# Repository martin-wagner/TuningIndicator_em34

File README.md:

TuningIndicator EM34

# TuningIndicator_EM34

Tube in operation

Tube in comparision to a Philips EM34

Youtube:

## Credits

This project is based on retronics.no 6U5 replacement: https://github.com/donpivo/TuningIndicator_6U5

All PCB design files (KiCAD), fabrication files (gerber), 3D models (.stl) and code (C++, PlatformIO) are shared for personal use only; not for commercial use / sale of neither the complete solution nor parts of it.

## Replacement

The EM34 tube is expensive to buy in good condition and doesn't last that long. "Alternative" tubes only have one shadow angles instead of two.
This project creates a long-lasting tube that mimics the two shadow angles of the EM34, including different sensitivity.

## Building

Follow the guide for the 6U5 tube, it's close enough to the EM34: https://retronics.no/2024/08/29/diy-digital-6u5-magic-eye-replacement/
Be aware to use the EM34 BOM, not the 6U5 one!

### LCD

Can be found on Ebay / Aliexpress for approx. 3 Euro. Search terms: _lcd 0.99 12pin_ . Writing _NFP099-01A_ .

### PCB / Housing

Use the gerbers/drill files in cad/pcb/mcu_board/pcb and cad/pcb/octal_base to order at the pcb house of your choise. Use Models/DisplayBracket.stl / Models/EM34-Tube and print/order at the print house of your choise. I've used JLCPCB / JLC3D.

- You need to check your radios schematic for connection of the cathode (see comment in octal_base.pdf).
- I did not use the EMI shield.

### Programming

Use platformio + ST SWD programmer. Either use the programmer on a STM32 devboard or get a ST-LINK/V2 (approx. 15 Euro). Jtag is also exposed on my board, but doesn't have a connector. Use jumper wires to connect SWD to the programmer. The board prints debug info on the serial port.
Be aware that the LCD will not be enabled without pulling the enable pin high (=anode voltage applied)!

### Problems

- The tube is larger compared to a original EM34 (diameter of the top part 30mm instead of 27mm, length 95mm instead of 85mm). Check if your radio will fit a tube of this size!
- The LCD doesn't have good color quality / resolution
- No tube visible when radio is powered off

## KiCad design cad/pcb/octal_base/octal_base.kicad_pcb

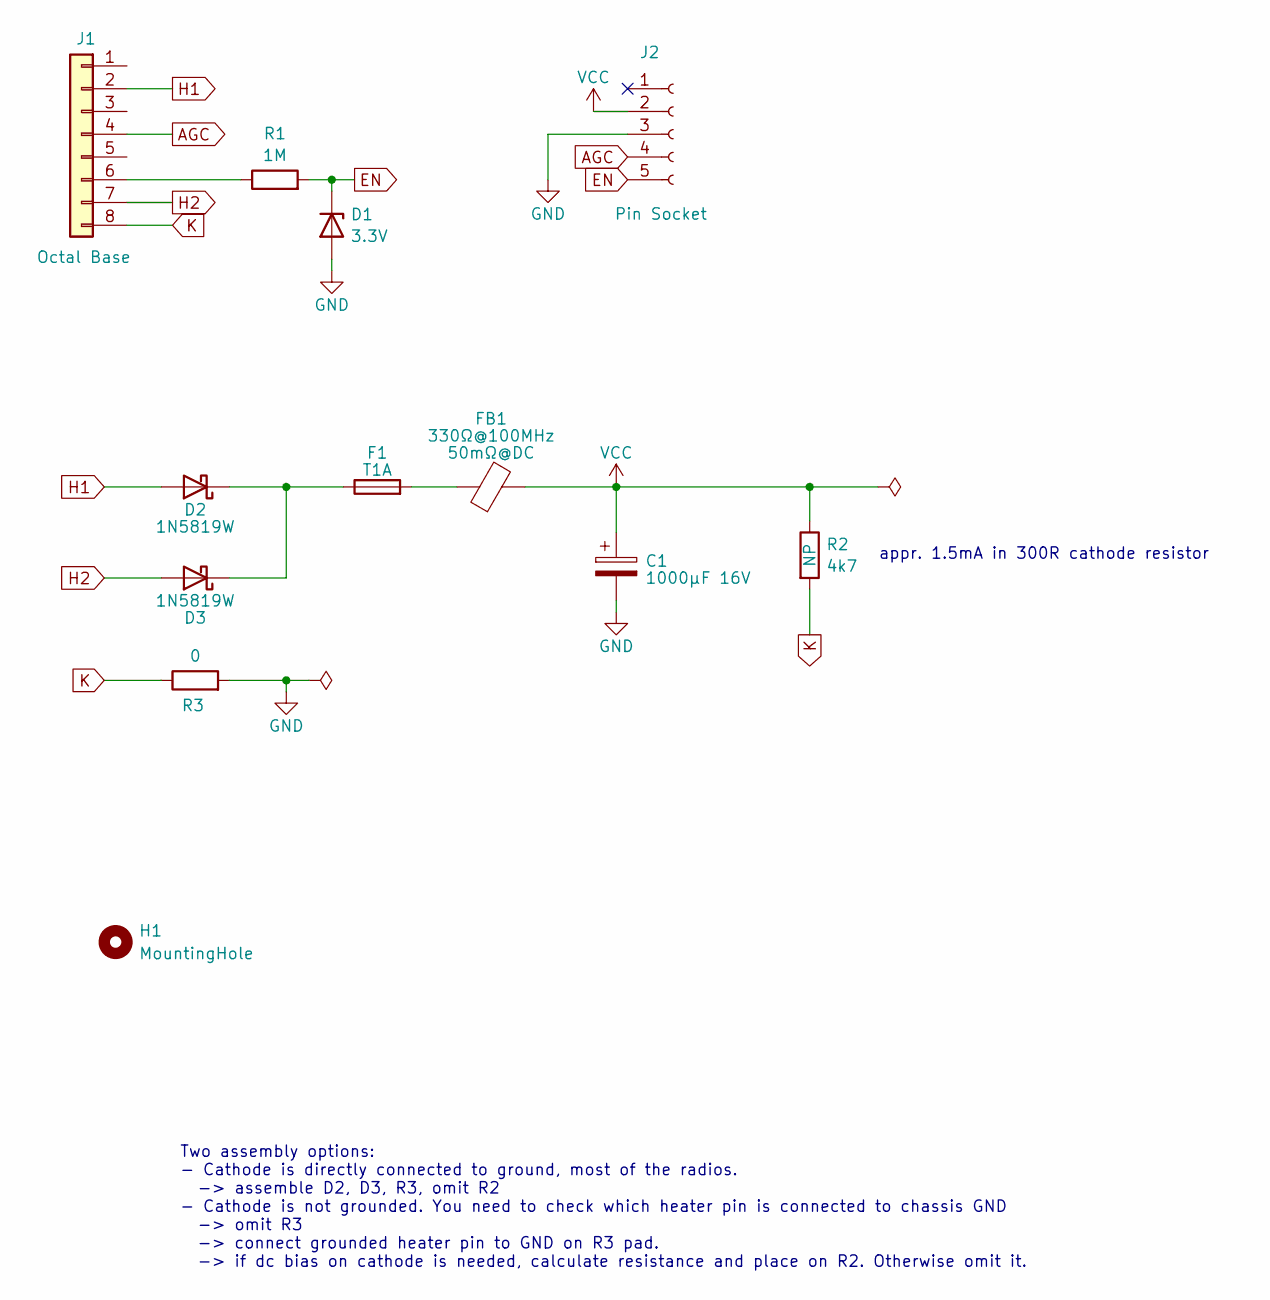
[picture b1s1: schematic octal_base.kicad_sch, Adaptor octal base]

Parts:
C1: 1000µF 16V; CP_Radial_D8.0mm_P3.50mm_H21mm
D1: 3.3V; D_0603_1608Metric_Pad1.05x0.95mm_HandSolder
D2, D3: 1N5819W; D_SOD-323_HandSoldering
F1: T1A; Fuse_1206_3216Metric
FB1: 330Ω@100MHz; L_0805_2012Metric_Pad1.15x1.40mm_HandSolder
H1: MountingHole; MountingHole_2.7mm_M2.5
J1: Octal Base; Valve_Octal_Base
J2: Pin Socket; PinSocket_1x05_P2.54mm_Vertical
R1: 1M; R_1206_3216Metric_Pad1.30x1.75mm_HandSolder
R2: 4k7; R_0603_1608Metric_Pad0.98x0.95mm_HandSolder
R3: 0; R_0603_1608Metric_Pad0.98x0.95mm_HandSolder

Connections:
AGC: J1.4, J2.4
EN: D1.1 (K), J2.5, R1.2
GND: C1.2, D1.2 (A), J2.3, R3.2
H1: D2.2 (A), J1.2
H2: D3.2 (A), J1.7
K: J1.8, R2.2, R3.1
unnamed: D2.1 (K), D3.1 (K), F1.1
unnamed: F1.2, FB1.1
unnamed: J1.6, R1.1
VCC: C1.1, FB1.2, J2.2, R2.1

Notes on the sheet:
appr. 1.5mA in 300R cathode resistor
Two assembly options: - Cathode is directly connected to ground, most of the radios. -> assemble D2, D3, R3, omit R2 - Cathode is not grounded. You need to check which heater pin is connected to chassis GND -> omit R3 -> connect grounded heater pin to GND on R3 pad. -> if dc bias on cathode is need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

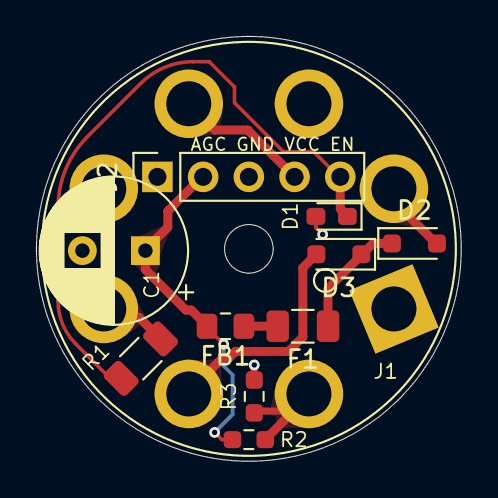
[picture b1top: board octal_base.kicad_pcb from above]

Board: 2 copper layers, 23.6 x 23.6 mm, 12 parts (0 on the bottom side), 10 nets.

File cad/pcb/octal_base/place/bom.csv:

"Source:","/home/martin/elektronik/radios/TuningIndicator_em34/cad/pcb/octal_base/octal_base.kicad_sch"
"Date:","2025-08-21T12:49:58+0200"
"Tool:","Eeschema 9.0.4-9.0.4-0~ubuntu24.04.1"
"Generator:","/usr/share/kicad/plugins/bom_csv_grouped_by_value.py"
"Component Count:","11"

"Collated Components:"

"Item","Qty","Reference(s)","Value","LibPart","Footprint","Datasheet","DNP","Comments","Datasheet","Description","Footprint","Placement"
"1","1","C1","1000µF 16V","Device:C_Polarized","CP_Radial_D8.0mm_P3.50mm_H21mm","~","","","~","Polarized capacitor","CP_Radial_D8.0mm_P3.50mm_H21mm",""
"2","1","D1","3.3V","Device:D_Zener","Diode_SMD:D_0603_1608Metric_Pad1.05x0.95mm_HandSolder","~","","","~","Zener diode","Diode_SMD:D_0603_1608Metric_Pad1.05x0.95mm_HandSolder",""
"3","2","D2, D3","1N5819W","Diode:1N5819WS","D_SOD-323_HandSoldering","https://datasheet.lcsc.com/lcsc/2204281430_Guangdong-Hottech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","","","https://datasheet.lcsc.com/lcsc/2204281430_Guangdong-Hottech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","40V 600mV@1A 1A SOD-323 Schottky Barrier Diodes, SOD-323","D_SOD-323_HandSoldering",""
"4","1","F1","T1A","Device:Fuse","Fuse_1206_3216Metric","~","","","~","Fuse","Fuse_1206_3216Metric",""
"5","1","FB1","330Ω@100MHz","Device:FerriteBead","L_0805_2012Metric_Pad1.15x1.40mm_HandSolder","~","","50mΩ@DC","~","Ferrite bead","L_0805_2012Metric_Pad1.15x1.40mm_HandSolder",""
"6","1","J1","Octal Base","Connector_Generic:Conn_01x08","Library:Valve_Octal_Base","~","","","~","Generic connector, single row, 01x08, script generated (kicad-library-utils/schlib/autogen/connector/)","Library:Valve_Octal_Base",""
"7","1","J2","Pin Socket","Connector:Conn_01x05_Socket","PinSocket_1x05_P2.54mm_Vertical","~","","","~","Generic connector, single row, 01x05, script generated","PinSocket_1x05_P2.54mm_Vertical",""
"8","1","R1","1M","Device:R","Resistor_SMD:R_1206_3216Metric_Pad1.30x1.75mm_HandSolder","~","","","~","Resistor","Resistor_SMD:R_1206_3216Metric_Pad1.30x1.75mm_HandSolder",""
"9","1","R2","4k7","Device:R","Resistor_SMD:R_0603_1608Metric_Pad0.98x0.95mm_HandSolder","~","","","~","Resistor","Resistor_SMD:R_0603_1608Metric_Pad0.98x0.95mm_HandSolder","NP"
"10","1","R3","0","Device:R","Resistor_SMD:R_0603_1608Metric_Pad0.98x0.95mm_HandSolder","~","","","~","Resistor","Resistor_SMD:R_0603_1608Metric_Pad0.98x0.95mm_HandSolder",""

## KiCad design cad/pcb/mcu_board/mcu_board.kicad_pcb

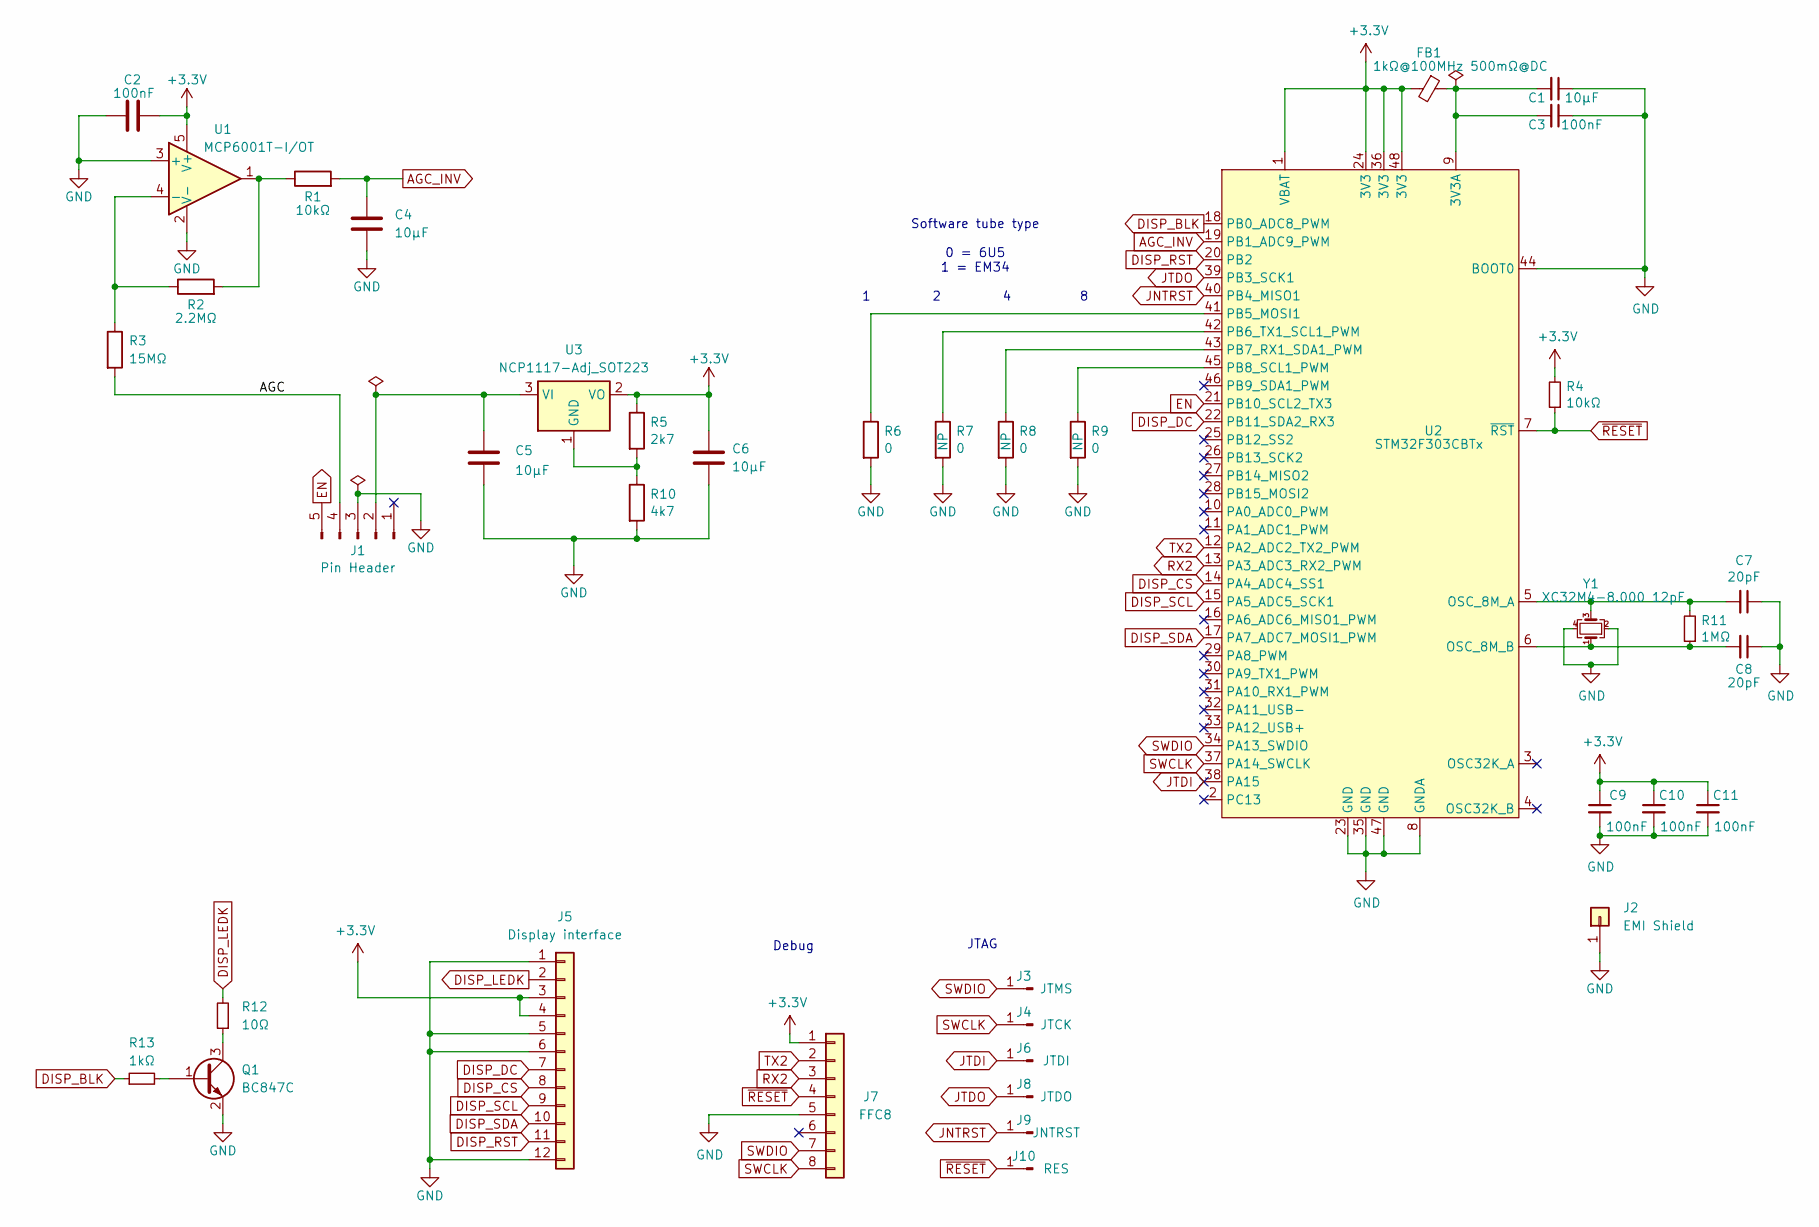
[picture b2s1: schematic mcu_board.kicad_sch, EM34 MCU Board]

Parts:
C1, C4, C5, C6: 10µF; C_1206_3216Metric_Pad1.33x1.80mm_HandSolder
C2, C3, C9, C10, C11: 100nF; C_0603_1608Metric_Pad1.08x0.95mm_HandSolder
C7, C8: 20pF; C_0603_1608Metric_Pad1.08x0.95mm_HandSolder
FB1: 1kΩ@100MHz 500mΩ@DC; L_0603_1608Metric_Pad1.05x0.95mm_HandSolder
J1: Pin Header; PinHeader_1x05_P2.54mm_Horizontal
J2: EMI Shield; EMI_Shield_MS207-10S
J3, J4, J6, J8, J9, J10: Conn_01x01_Pin; TestPoint_Pad_D1.5mm
J5: Display interface; 505110-1292
J7: FFC8; PinHeader_1x08_P2.54mm_Vertical
Q1: BC847C; SOT-23
R1, R4: 10kΩ; R_0603_1608Metric_Pad0.98x0.95mm_HandSolder
R2: 2.2MΩ; R_0603_1608Metric_Pad0.98x0.95mm_HandSolder
R3: 15MΩ; R_0603_1608Metric_Pad0.98x0.95mm_HandSolder
R5: 2k7; R_0603_1608Metric_Pad0.98x0.95mm_HandSolder
R6, R7, R8, R9: 0; R_0603_1608Metric_Pad0.98x0.95mm_HandSolder
R10: 4k7; R_0603_1608Metric_Pad0.98x0.95mm_HandSolder
R11: 1MΩ; R_0603_1608Metric_Pad0.98x0.95mm_HandSolder
R12: 10Ω; R_0603_1608Metric_Pad0.98x0.95mm_HandSolder
R13: 1kΩ; R_0603_1608Metric_Pad0.98x0.95mm_HandSolder
U1: MCP6001T-I/OT; SOT-23-5
U2: STM32F303CBTx; LQFP-48_7x7mm_P0.5mm
U3: NCP1117-Adj_SOT223; SOT-223-3_TabPin2
Y1: XC32M4-8.000 12pF; Crystal_SMD_3225-4Pin_3.2x2.5mm

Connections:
+3.3V: C2.2, C6.1, C9.1, C10.1, C11.1, FB1.2, J5.3, J5.4, J7.1, R4.2, R5.1, U1.5 (V+), U2.1 (VBAT), U2.24 (3V3), U2.36 (3V3), U2.48 (3V3), U3.2 (VO)
/AGC: J1.4, R3.2
AGC_INV: C4.1, R1.2, U2.19 (PB1_ADC9_PWM)
DISP_BLK: R13.1, U2.18 (PB0_ADC8_PWM)
DISP_CS: J5.8, U2.14 (PA4_ADC4_SS1)
DISP_DC: J5.7, U2.22 (PB11_SDA2_RX3)
DISP_LEDK: J5.2, R12.2
DISP_RST: J5.11, U2.20 (PB2)
DISP_SCL: J5.9, U2.15 (PA5_ADC5_SCK1)
DISP_SDA: J5.10, U2.17 (PA7_ADC7_MOSI1_PWM)
EN: J1.5, U2.21 (PB10_SCL2_TX3)
GND: C1.1, C2.1, C3.1, C4.2, C5.2, C6.2, C7.1, C8.1, C9.2, C10.2, C11.2, J1.3, J2.1, J5.1, J5.5, J5.6, J5.12, J7.5, Q1.2 (E), R6.2, R7.2, R8.2, R9.2, R10.2, U1.2 (V-), U1.3 (+), U2.8 (GNDA), U2.23 (GND), U2.35 (GND), U2.44 (BOOT0), U2.47 (GND), Y1.2, Y1.4
JNTRST: J9.1, U2.40 (PB4_MISO1)
JTDI: J6.1, U2.38 (PA15)
JTDO: J8.1, U2.39 (PB3_SCK1)
unnamed: C5.1, J1.2, U3.3 (VI)
unnamed: Q1.1 (B), R13.2
unnamed: Q1.3 (C), R12.1
unnamed: R1.1, R2.2, U1.1
unnamed: R2.1, R3.1, U1.4 (-)
unnamed: C1.2, C3.2, FB1.1, U2.9 (3V3A)
unnamed: C7.2, R11.2, U2.5 (OSC_8M_A), Y1.3
unnamed: C8.2, R11.1, U2.6 (OSC_8M_B), Y1.1
unnamed: R6.1, U2.41 (PB5_MOSI1)
unnamed: R7.1, U2.42 (PB6_TX1_SCL1_PWM)
unnamed: R8.1, U2.43 (PB7_RX1_SDA1_PWM)
unnamed: R9.1, U2.45 (PB8_SCL1_PWM)
unnamed: R5.2, R10.1, U3.1 (GND)
RX2: J7.3, U2.13 (PA3_ADC3_RX2_PWM)
SWCLK: J4.1, J7.8, U2.37 (PA14_SWCLK)
SWDIO: J3.1, J7.7, U2.34 (PA13_SWDIO)
TX2: J7.2, U2.12 (PA2_ADC2_TX2_PWM)
~RESET: J7.4, J10.1, R4.1, U2.7 (~RST)

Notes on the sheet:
JTAG
Debug
Software tube type 0 = 6U5 1 = EM34 1 2 4 8

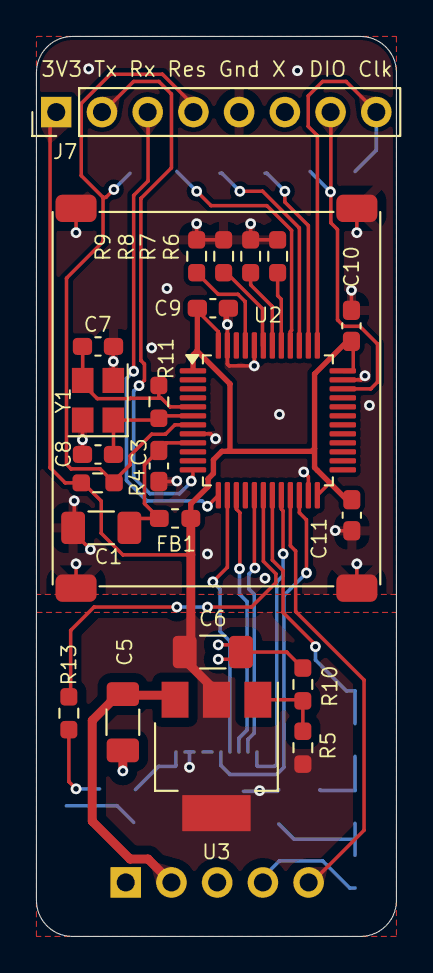
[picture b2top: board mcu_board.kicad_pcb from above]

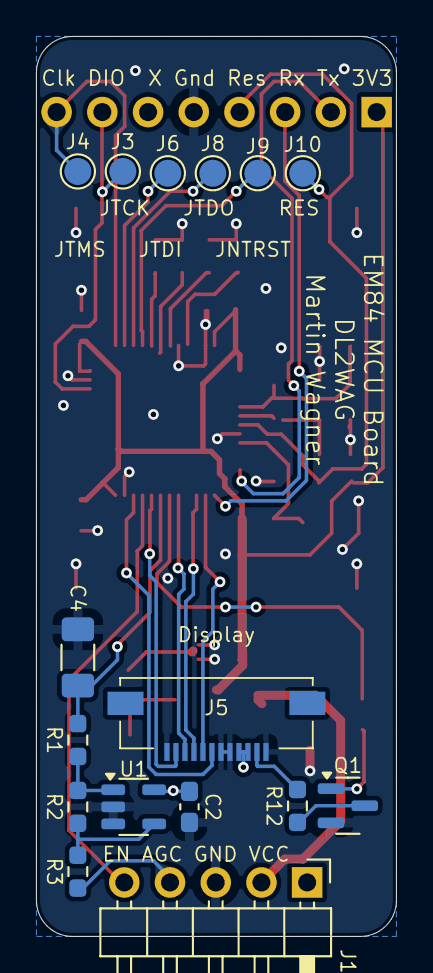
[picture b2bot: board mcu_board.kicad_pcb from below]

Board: 2 copper layers, 20.0 x 50.0 mm, 40 parts (16 on the bottom side), 33 nets.

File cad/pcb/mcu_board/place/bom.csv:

"Source:","/home/martin/elektronik/radios/TuningIndicator_em34/cad/pcb/mcu_board/mcu_board.kicad_sch"
"Date:","2025-01-07T12:11:06+0100"
"Tool:","Eeschema 8.0.7-8.0.7-0~ubuntu22.04.1"
"Generator:","/usr/share/kicad/plugins/bom_csv_grouped_by_value.py"
"Component Count:","40"

"Collated Components:"

"Item","Qty","Reference(s)","Value","LibPart","Footprint","Datasheet","DNP","Comments","Datasheet","Description","Footprint","Place"
"1","1","C1","10µF","Device:C_Small","Capacitor_SMD:C_1206_3216Metric_Pad1.33x1.80mm_HandSolder","~","","","~","Unpolarized capacitor, small symbol","Capacitor_SMD:C_1206_3216Metric_Pad1.33x1.80mm_HandSolder",""
"2","1","C2","100nF","Device:C","Retronics_Passives:C_0603_1608Metric_Pad1.08x0.95mm_HandSolder","~","","","~","Unpolarized capacitor","Retronics_Passives:C_0603_1608Metric_Pad1.08x0.95mm_HandSolder",""
"3","4","C3, C9, C10, C11","100nF","Device:C_Small","Capacitor_SMD:C_0603_1608Metric_Pad1.08x0.95mm_HandSolder","~","","","~","Unpolarized capacitor, small symbol","Capacitor_SMD:C_0603_1608Metric_Pad1.08x0.95mm_HandSolder",""
"4","3","C4, C5, C6","10µF","Device:C","Capacitor_SMD:C_1206_3216Metric_Pad1.33x1.80mm_HandSolder","~","","","~","Unpolarized capacitor","Capacitor_SMD:C_1206_3216Metric_Pad1.33x1.80mm_HandSolder",""
"5","2","C7, C8","20pF","Device:C_Small","Capacitor_SMD:C_0603_1608Metric_Pad1.08x0.95mm_HandSolder","~","","","~","Unpolarized capacitor, small symbol","Capacitor_SMD:C_0603_1608Metric_Pad1.08x0.95mm_HandSolder",""
"6","1","FB1","1kΩ@100MHz 500mΩ@DC","Device:FerriteBead_Small","Inductor_SMD:L_0603_1608Metric_Pad1.05x0.95mm_HandSolder","~","","","~","Ferrite bead, small symbol","Inductor_SMD:L_0603_1608Metric_Pad1.05x0.95mm_HandSolder",""
"7","1","J1","Pin Header","Connector:Conn_01x05_Pin","Connector_PinHeader_2.54mm:PinHeader_1x05_P2.54mm_Horizontal","~","","","~","Generic connector, single row, 01x05, script generated","Connector_PinHeader_2.54mm:PinHeader_1x05_P2.54mm_Horizontal",""
"8","1","J2","EMI Shield","Connector_Generic:Conn_01x01","Retronics_Hardware:EMI_Shield_MS207-10S","~","","","~","Generic connector, single row, 01x01, script generated (kicad-library-utils/schlib/autogen/connector/)","Retronics_Hardware:EMI_Shield_MS207-10S",""
"9","6","J3, J4, J6, J8, J9, J10","Conn_01x01_Pin","Connector:Conn_01x01_Pin","TestPoint:TestPoint_Pad_D1.5mm","~","","","~","JTMS","TestPoint:TestPoint_Pad_D1.5mm",""
"10","1","J5","Display interface","Connector_Generic:Conn_01x12","Retronics_Connectors:505110-1292","~","","","~","Generic connector, single row, 01x12, script generated (kicad-library-utils/schlib/autogen/connector/)","Retronics_Connectors:505110-1292",""
"11","1","J7","FFC8","Connector_Generic:Conn_01x08","Connector_PinHeader_2.54mm:PinHeader_1x08_P2.54mm_Vertical","~","","","~","Generic connector, single row, 01x08, script generated (kicad-library-utils/schlib/autogen/connector/)","Connector_PinHeader_2.54mm:PinHeader_1x08_P2.54mm_Vertical",""
"12","1","Q1","BC847C","Transistor_BJT:BC847","Retronics_Discrete:SOT-23","http://www.infineon.com/dgdl/Infineon-BC847SERIES_BC848SERIE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","","","http://www.infineon.com/dgdl/Infineon-BC847SERIES_BC848SERIE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","0.1A Ic, 45V Vce, NPN Transistor, SOT-23","Retronics_Discrete:SOT-23",""
"13","1","R1","10kΩ","Device:R","Retronics_Passives:R_0603_1608Metric_Pad0.98x0.95mm_HandSolder","~","","","~","Resistor","Retronics_Passives:R_0603_1608Metric_Pad0.98x0.95mm_HandSolder",""
"14","1","R2","2.2MΩ","Device:R","Retronics_Passives:R_0603_1608Metric_Pad0.98x0.95mm_HandSolder","~","","","~","Resistor","Retronics_Passives:R_0603_1608Metric_Pad0.98x0.95mm_HandSolder",""
"15","1","R3","15MΩ","Device:R","Retronics_Passives:R_0603_1608Metric_Pad0.98x0.95mm_HandSolder","~","","","~","Resistor","Retronics_Passives:R_0603_1608Metric_Pad0.98x0.95mm_HandSolder",""
"16","1","R4","10kΩ","Device:R_Small","Resistor_SMD:R_0603_1608Metric_Pad0.98x0.95mm_HandSolder","~","","","~","Resistor, small symbol","Resistor_SMD:R_0603_1608Metric_Pad0.98x0.95mm_HandSolder",""
"17","1","R5","2k7","Device:R","Resistor_SMD:R_0603_1608Metric_Pad0.98x0.95mm_HandSolder","~","","","~","Resistor","Resistor_SMD:R_0603_1608Metric_Pad0.98x0.95mm_HandSolder",""
"18","4","R6, R7, R8, R9","0","Device:R","Resistor_SMD:R_0603_1608Metric_Pad0.98x0.95mm_HandSolder","~","","","~","Resistor","Resistor_SMD:R_0603_1608Metric_Pad0.98x0.95mm_HandSolder","NP"
"19","1","R10","4k7","Device:R","Resistor_SMD:R_0603_1608Metric_Pad0.98x0.95mm_HandSolder","~","","","~","Resistor","Resistor_SMD:R_0603_1608Metric_Pad0.98x0.95mm_HandSolder",""
"20","1","R11","1MΩ","Device:R_Small","Resistor_SMD:R_0603_1608Metric_Pad0.98x0.95mm_HandSolder","~","","","~","Resistor, small symbol","Resistor_SMD:R_0603_1608Metric_Pad0.98x0.95mm_HandSolder",""
"21","1","R12","10Ω","Device:R_Small","Resistor_SMD:R_0603_1608Metric_Pad0.98x0.95mm_HandSolder","~","","","~","Resistor, small symbol","Resistor_SMD:R_0603_1608Metric_Pad0.98x0.95mm_HandSolder",""
"22","1","R13","1kΩ","Device:R_Small","Resistor_SMD:R_0603_1608Metric_Pad0.98x0.95mm_HandSolder","~","","","~","Resistor, small symbol","Resistor_SMD:R_0603_1608Metric_Pad0.98x0.95mm_HandSolder",""
"23","1","U1","MCP6001T-I/OT","Amplifier_Operational:MCP601-xOT","Retronics_IC:SOT-23-5","http://ww1.microchip.com/downloads/en/DeviceDoc/21314g.pdf","","","http://ww1.microchip.com/downloads/en/DeviceDoc/21314g.pdf","Single 2.7V to 6.0V Single Supply CMOS Op Amps, SOT-23-5","Retronics_IC:SOT-23-5",""
"24","1","U2","STM32F303CBTx","Retronics_Microcontrollers:STM32F103Cx","Package_QFP:LQFP-48_7x7mm_P0.5mm","http://www.st.com/st-web-ui/static/active/en/resource/techni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","","","http://www.st.com/st-web-ui/static/active/en/resource/techni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","ARM Cortex-M4 MCU, 128KB flash, 40KB RAM, 72MHz, 2-3.6V, 37 GPIO, LQFP-48","Package_QFP:LQFP-48_7x7mm_P0.5mm",""
"25","1","U3","NCP1117-Adj_SOT223","Regulator_Linear:NCP1117-5.0_SOT223","Retronics_IC_Power:SOT-223-3_TabPin2","http://www.onsemi.com/pub_link/Collateral/NCP1117-D.PDF","","","http://www.onsemi.com/pub_link/Collateral/NCP1117-D.PDF","1A Low drop-out regulator, Fixed Output 5V, SOT-223","Retronics_IC_Power:SOT-223-3_TabPin2",""
"26","1","Y1","XC32M4-8.000 12pF","Device:Crystal_GND24_Small","Crystal:Crystal_SMD_3225-4Pin_3.2x2.5mm","~","","","~","Four pin crystal, GND on pins 2 and 4, small symbol","Crystal:Crystal_SMD_3225-4Pin_3.2x2.5mm",""

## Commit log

2025-01-06 Add: original project doc, Change: move files
2025-01-06 add: cad gitignore
2025-01-06 Change: Use octal socket, Add: Anode voltage detection
    change pin socket to 5way
    - more stability
    - extra pin
2025-01-06 Change: Pcb to octal
2025-01-06 Change: Schematic 6U5 -> EM34
    - use generic 1117
    - add software selection straps
2025-01-06 Fix: EM34 commonly uses cathode resistor, can't use k as gnd
2025-01-07 Change: Update uC PCB
2025-01-07 Change: Add Jtag, Cleanup
2025-01-07 Add: Base Cleanup
2025-01-07 Add: manufacturing files
2025-01-07 Change: Cleanup
2025-03-22 Add: Hardware bring-up
2025-04-05 Fix LCD offset, removing two random pixel columns on the side...
    as seen in the blog, second image:
    https://retronics.no/2024/08/29/diy-digital-6u5-magic-eye-replacement/
    https://retronics.no/wp-content/uploads/2024/07/20240714_102917.jpg
2025-04-05 New: EM34 has two eye openings
2025-04-05 New: two display ranges. top 4x sensitivity of bottom
2025-04-05 change: math function following philips datasheet...
    Philips EM 34 1.1.1956 939 1445 plot "B"
2025-04-06 Add: Type detection, enable pin (anode voltage detection)
2025-04-06 Change: folder name
2025-04-06 Formatter commit
2025-04-06 Change: make classes, preparation for supporting different tube types
2025-08-21 Fix: EM34 socket, don't use bridge rect...
    gnd floats at approx. 1/2 vcc relative to chassis-gnd -- oops.
2025-08-21 Change: modified colors
2025-08-21 Change: re-added 6U5
2025-11-29 Add: 3d model em34
2025-11-29 Add: Sim rect/op
2025-11-29 Add: readme
2025-11-29 Fix: Markdown links
2025-11-29 Nochmal Markdown
